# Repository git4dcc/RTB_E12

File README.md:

# RTB_E12

This module implements a compact 12-channel WS2811 PCB designed to fit within a signal's socket. Connectivity is provided via an FFC cable to an adapter board (P15) mounted beneath the layout, which allows the signal to be easily detached—for example, during transportation. The E12 can be cascaded with other WS28xx compatible chips.

<details>
<summary>See also</summary>

- [RTB_E10](https://github.com/git4dcc/RTB_E10)
- [RTB_E13](https://github.com/git4dcc/RTB_E13)
- [RTB_E15](https://github.com/git4dcc/RTB_E15)

</details>

<details>
<summary>User Guides</summary>

- [User Guide - DE](https://rtb4dcc.de/ws2811_guide_de/)
- User Guide - EN

</details>

The module has the following features,
- **Protocol**
  - WS2811 chip protocol
- **LED ports**
  - fixed 12 channel (4x WS2811 chips)
  - +5V common LED voltage (common anode)
  - 255 step PWM

# Hardware
The PCB layout uses SMD footprints with 0.5mm pitch and 0402 parts. Reflow soldering is mandatory.

The hardware does pull operation with 5V common.

## PCB
- 4-layer PCB, FR4, 0.8mm, 18x6mm
- CPU: none (native WS2811 chips)
- BUS: WS2811
- LED: pull /w common anode
<br>

**Top**

**Bottom**

[Schematic](doc/E12_schematic.pdf) | [Layout](doc/E12_layout.pdf) | [Gerber](gerber)

## Firmware
This module does **not** have any firmware code (uses native WS2811 chips).

# Use Case
The E12 module is housed within the signal's socket and links to the adapter, located beneath the layout, through a flexible flat cable (FFC).

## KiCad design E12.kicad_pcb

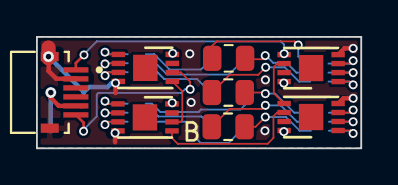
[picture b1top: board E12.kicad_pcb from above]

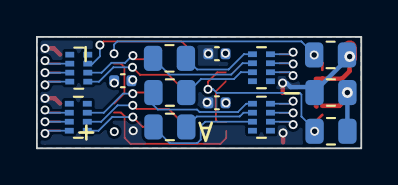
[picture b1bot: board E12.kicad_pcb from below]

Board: 4 copper layers, 18.0 x 6.2 mm, 21 parts (13 on the bottom side), 31 nets.

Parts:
C1, C2, C3: 100n; C_0402_1005Metric
J3: FFC; AMPHENOL_59453-061110EDHLF
R1, R2, R3, R4, R5, R6, R9, R11, R12: n.f.; R_0805_2012Metric
RN1, RN2, RN3, RN4: 220; R_Array_Concave_4x0402
U1, U2, U3, U4: WS2811; DFN-8-1EP_3x2mm_P0.5mm_EP1.36x1.46mm

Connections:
DI: J3.6, R12.1, U1.6
DO: J3.1, R11.1, U4.5
GND: C1.2, C2.2, C3.2, J3.2, J3.7, J3.8, R9.2, R11.2, U1.4, U2.4, U3.4, U4.4
unnamed: U1.5, U2.6
unnamed: U2.5, U3.6
unnamed: U3.5, U4.6
OUT0: RN1.4, U1.1
OUT1: RN1.3, U1.2
OUT2: RN1.2, U1.3
OUT3: RN2.4, U2.1
OUT4: RN2.3, U2.2
OUT5: RN2.2, U2.3
OUT6: RN4.4, U3.1
OUT7: RN4.3, U3.2
OUT8: RN4.2, U3.3
OUT9: RN3.4, U4.1
OUT10: RN3.3, U4.2
OUT11: RN3.2, U4.3
Port-0: R4.2, RN1.5
Port-1: R4.1, RN1.6
Port-2: R5.2, RN1.7
Port-3: R5.1, RN2.5
Port-4: R6.2, RN2.6
Port-5: R6.1, RN2.7
Port-6: R3.1, RN4.5
Port-7: R3.2, RN4.6
Port-8: R2.1, RN4.7
Port-9: R2.2, RN3.5
Port-10: R1.1, RN3.6
Port-11: R1.2, RN3.7
VDD: C1.1, C2.1, C3.1, J3.5, R9.1, R12.2, U1.8, U2.8, U3.8, U4.8

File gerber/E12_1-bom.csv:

Value,Designator,Footprint,JLCPCB Part#,Description
100n,"C1,C2,C3",Capacitor_SMD:C_0402_1005Metric,C14663,100nF 50V X7R ñ10% 0603 Multilayer Ceramic Capacitors MLCC - SMD/SMT ROHS
FFC,J3,AMPHENOL_59453-061110EDHLF,C3169668,"-55?~+85? 0.3mm 0.5mm 0.88mm 6P Bottom Contact Copper Alloy Gold Slide Lock Surface Mount, Right Angle SMD,P=0.5mm,Surface Mount?Right Angle FFC, FPC (Flat Flexible) Connector Assemblies ROHS"
220,"RN1,RN2,RN3,RN4",Resistor_SMD:R_Array_Concave_4x0402,C25498,"1/16W 220ê 4 8 ñ200ppm/? ñ5% 0402x4 Resistor Networks, Arrays ROHS"
WS2811,"U1,U2,U3,U4",Package_DFN_QFN:DFN-8-1EP_3x2mm_P0.5mm_EP1.36x1.46mm,C3034985,-40?~+85? 16.5mA 20V 3 5V~24V 800kHz PWM VSON-8-EP(2x3) LED Drivers ROHS

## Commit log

2024-02-25 initial
2025-09-06 mod: optimized for PCB assembly

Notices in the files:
README.md:
Apache License 2.0
